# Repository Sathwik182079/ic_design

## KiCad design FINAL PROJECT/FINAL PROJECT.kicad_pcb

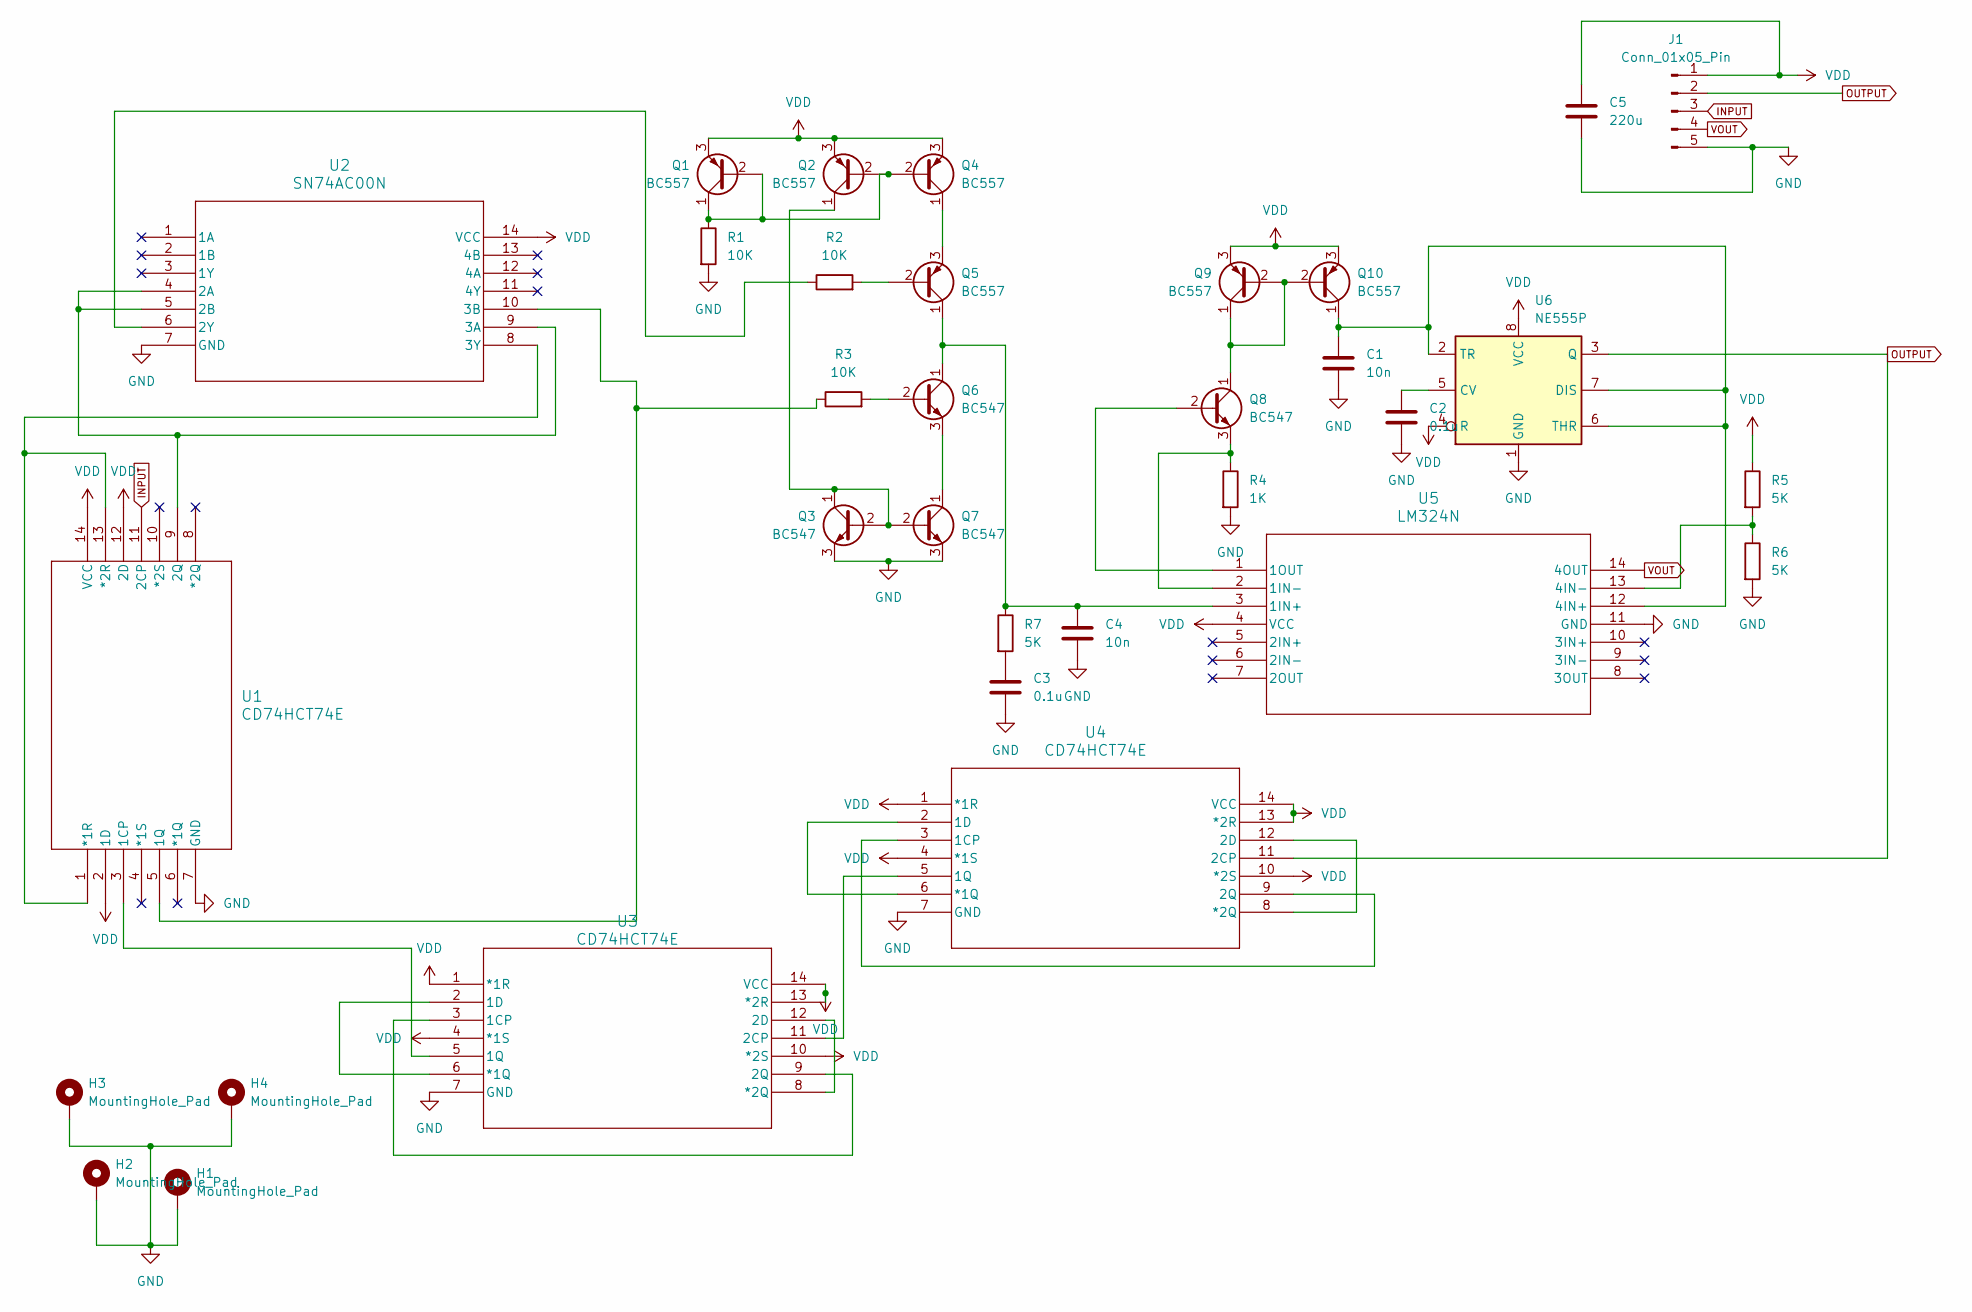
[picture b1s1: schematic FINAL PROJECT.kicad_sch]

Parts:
C1, C4: 10n; C_Disc_D7.5mm_W5.0mm_P5.00mm
C2, C3: 0.1u; C_Disc_D3.4mm_W2.1mm_P2.50mm
C5: 220u; C_Axial_L3.8mm_D2.6mm_P12.50mm_Horizontal
H1, H2, H3, H4: MountingHole_Pad; MountingHole_2.5mm_Pad
J1: Conn_01x05_Pin; PinHeader_1x05_P2.54mm_Vertical
Q1, Q2, Q4, Q5, Q9, Q10: BC557; TO-92_Inline
Q3, Q6, Q7, Q8: BC547; TO-92_Inline
R1, R2, R3: 10K; R_Axial_DIN0207_L6.3mm_D2.5mm_P7.62mm_Horizontal
R4: 1K; R_Axial_DIN0207_L6.3mm_D2.5mm_P7.62mm_Horizontal
R5, R6, R7: 5K; R_Axial_DIN0207_L6.3mm_D2.5mm_P7.62mm_Horizontal
U1, U3, U4: CD74HCT74E; 74HCT74
U2: SN74AC00N; N14
U5: LM324N; LM324
U6: NE555P; DIP-8_W7.62mm

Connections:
GND: C1.2, C2.2, C3.2, C4.2, C5.2, H1.1, H2.1, H3.1, H4.1, J1.5, Q3.3 (E), Q7.3 (E), R1.2, R4.2, R6.2, U1.7 (GND), U2.7 (GND), U3.7 (GND), U4.7 (GND), U5.11 (GND), U6.1 (GND)
INPUT: J1.3, U1.11 (2CP)
unnamed: C3.1, R7.2
unnamed: Q1.1 (C), Q1.2 (B), Q2.2 (B), Q4.2 (B), R1.1
unnamed: Q2.1 (C), Q3.1 (C), Q3.2 (B), Q7.2 (B)
unnamed: Q4.1 (C), Q5.3 (E)
unnamed: Q5.2 (B), R2.2
unnamed: C4.1, Q5.1 (C), Q6.1 (C), R7.1, U5.3 (1IN+)
unnamed: Q6.2 (B), R3.2
unnamed: Q6.3 (E), Q7.1 (C)
unnamed: Q8.2 (B), U5.1 (1OUT)
unnamed: Q8.3 (E), R4.1, U5.2 (1IN-)
unnamed: Q8.1 (C), Q9.1 (C), Q9.2 (B), Q10.2 (B)
unnamed: C1.1, Q10.1 (C), U5.12 (4IN+), U6.2 (TR), U6.6 (THR), U6.7 (DIS)
unnamed: U1.3 (1CP), U3.5 (1Q)
unnamed: R3.1, U1.5 (1Q), U2.10 (3B)
unnamed: U1.9 (2Q), U2.4 (2A), U2.5 (2B), U2.9 (3A)
unnamed: U1.1 (*1R), U1.13 (*2R), U2.8 (3Y)
unnamed: R2.1, U2.6 (2Y)
unnamed: U3.3 (1CP), U3.9 (2Q)
unnamed: U3.11 (2CP), U4.5 (1Q)
unnamed: U3.2 (1D), U3.6 (*1Q)
unnamed: U3.8 (*2Q), U3.12 (2D)
unnamed: U4.3 (1CP), U4.9 (2Q)
unnamed: U4.2 (1D), U4.6 (*1Q)
unnamed: U4.8 (*2Q), U4.12 (2D)
unnamed: R5.2, R6.1, U5.13 (4IN-)
unnamed: C2.1, U6.5 (CV)
OUTPUT: J1.2, U4.11 (2CP), U6.3 (Q)
VDD: C5.1, J1.1, Q1.3 (E), Q2.3 (E), Q4.3 (E), Q9.3 (E), Q10.3 (E), R5.1, U1.2 (1D), U1.12 (2D), U1.14 (VCC), U2.14 (VCC), U3.1 (*1R), U3.4 (*1S), U3.10 (*2S), U3.13 (*2R), U3.14 (VCC), U4.1 (*1R), U4.4 (*1S), U4.10 (*2S), U4.13 (*2R), U4.14 (VCC), U5.4 (VCC), U6.4 (R), U6.8 (VCC)
VOUT: J1.4, U5.14 (4OUT)

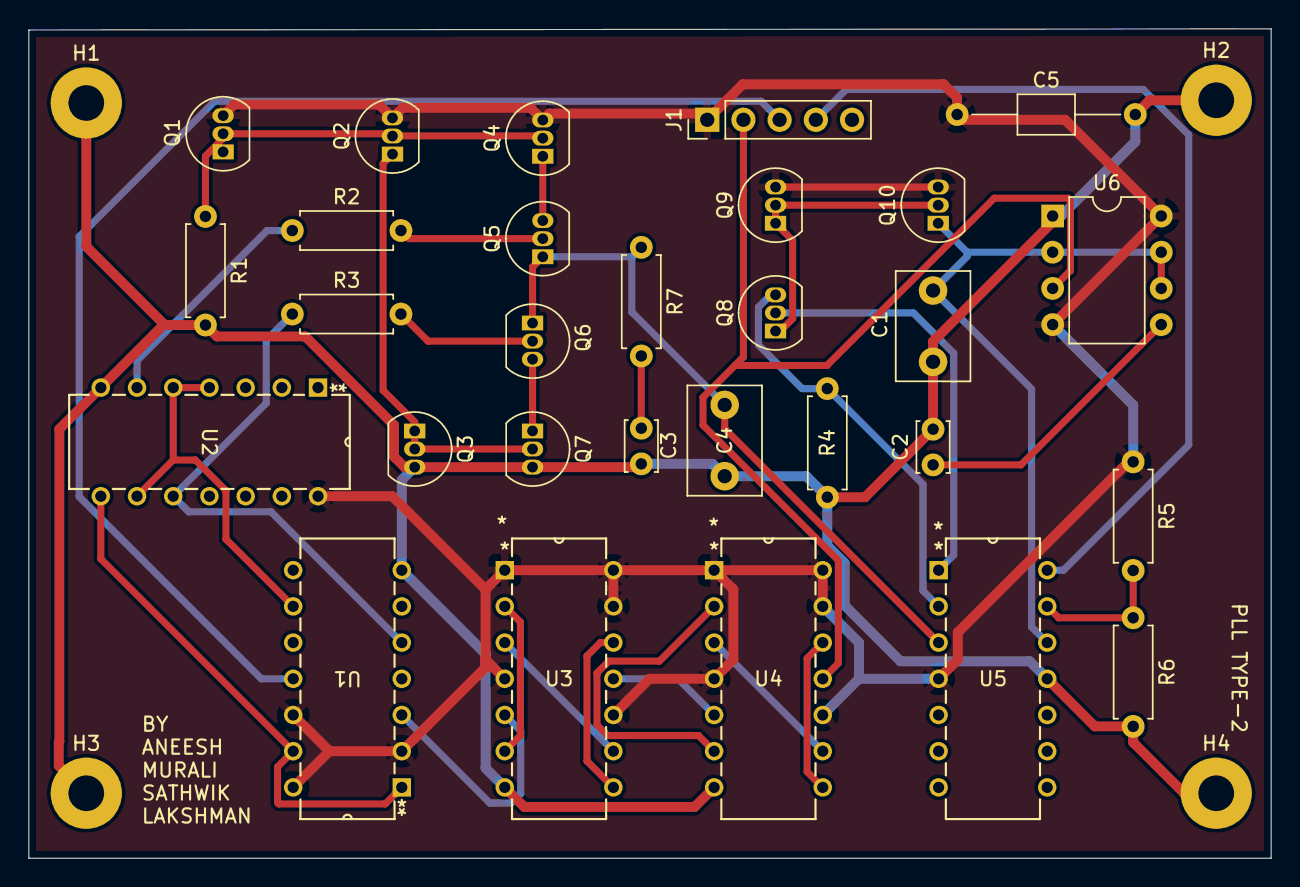
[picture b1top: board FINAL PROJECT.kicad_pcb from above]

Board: 2 copper layers, 87.2 x 58.2 mm, 33 parts (0 on the bottom side), 31 nets.
